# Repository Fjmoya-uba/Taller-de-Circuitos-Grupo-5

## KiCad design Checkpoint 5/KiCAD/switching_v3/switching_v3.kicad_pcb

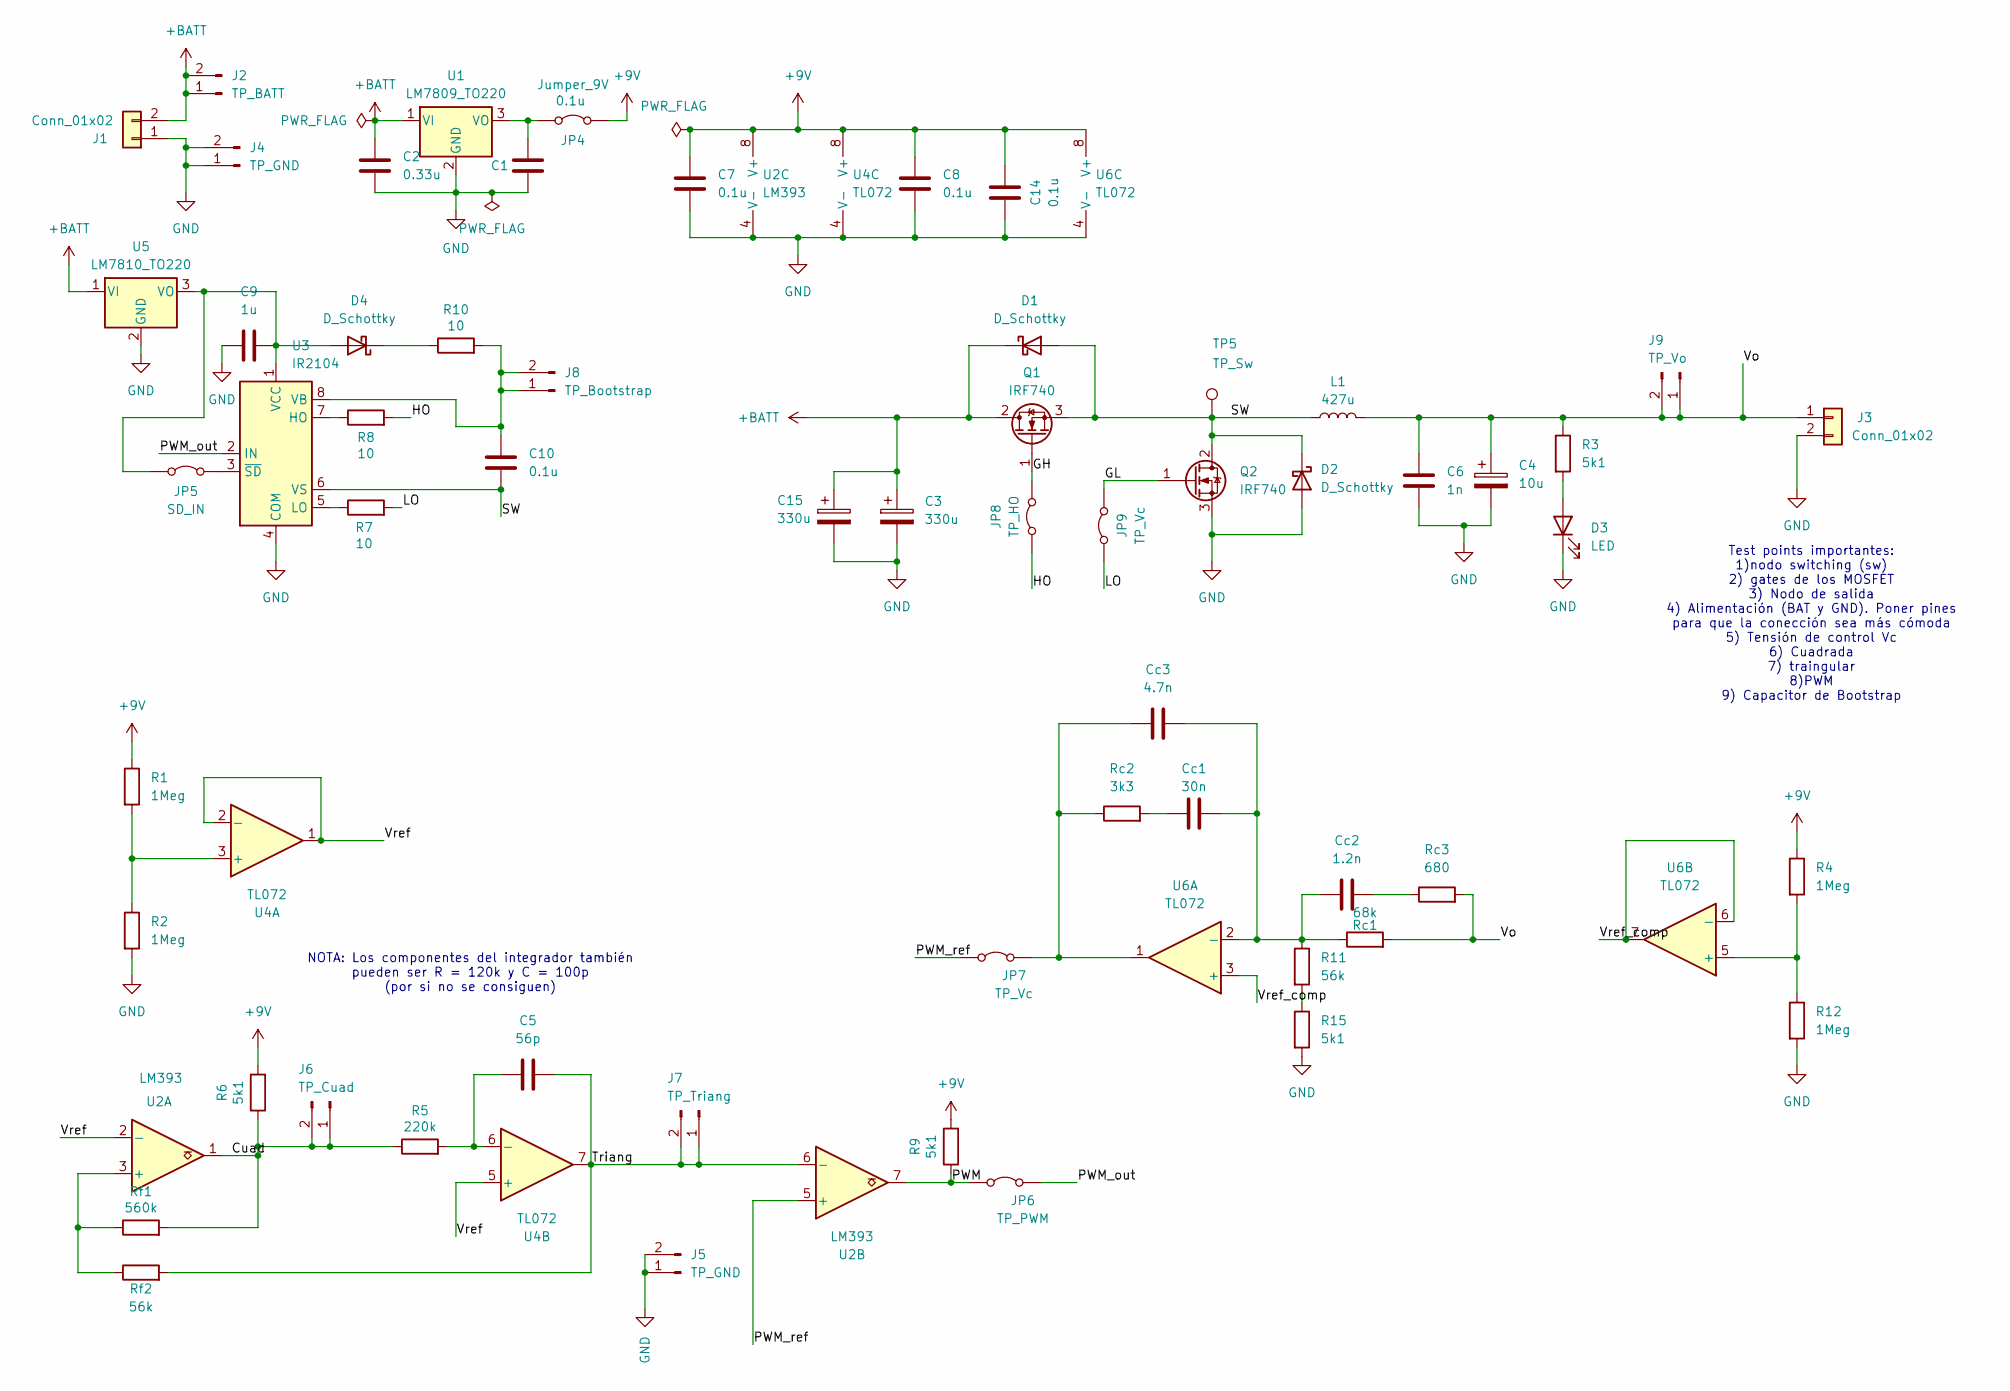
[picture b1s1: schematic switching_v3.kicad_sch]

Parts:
C1, C7, C8, C10, C14: 0.1u; C_Disc_D5.0mm_W2.5mm_P2.50mm
C2: 0.33u; C_Disc_D5.0mm_W2.5mm_P2.50mm
C3, C15: 330u; CP_Radial_D10.0mm_P5.00mm
C4: 10u; CP_Radial_D5.0mm_P2.50mm
C5: 56p; C_Disc_D5.0mm_W2.5mm_P2.50mm
C6: 1n; C_Disc_D14.5mm_W5.0mm_P10.00mm
C9: 1u; C_Disc_D8.0mm_W2.5mm_P5.00mm
Cc1: 30n; C_Disc_D5.0mm_W2.5mm_P2.50mm
Cc2: 1.2n; C_Disc_D5.0mm_W2.5mm_P2.50mm
Cc3: 4.7n; C_Disc_D5.0mm_W2.5mm_P2.50mm
D1, D2, D4: D_Schottky; D_DO-201AD_P12.70mm_Horizontal
D3: LED; LED_D5.0mm_IRGrey
J1, J3: Conn_01x02; TerminalBlock_MaiXu_MX126-5.0-02P_1x02_P5.00mm
J2: TP_BATT; PinHeader_1x02_P2.54mm_Vertical
J4, J5: TP_GND; PinHeader_1x02_P2.54mm_Vertical
J6: TP_Cuad; PinHeader_1x02_P2.54mm_Vertical
J7: TP_Triang; PinHeader_1x02_P2.54mm_Vertical
J8: TP_Bootstrap; PinHeader_1x02_P2.54mm_Vertical
J9: TP_Vo; PinHeader_1x02_P2.54mm_Vertical
JP4: Jumper_9V; PinHeader_1x02_P2.54mm_Vertical
JP5: SD_IN; PinHeader_1x02_P2.54mm_Vertical
JP6: TP_PWM; PinHeader_1x02_P2.54mm_Vertical
JP7, JP9: TP_Vc; PinHeader_1x02_P2.54mm_Vertical
JP8: TP_HO; PinHeader_1x02_P2.54mm_Vertical
L1: 427u; Transformer_37x44
Q1, Q2: IRF740; TO-220-3_Vertical
R1, R2, R4, R12: 1Meg; R_Axial_DIN0207_L6.3mm_D2.5mm_P7.62mm_Horizontal
R3, R6, R9, R15: 5k1; R_Axial_DIN0207_L6.3mm_D2.5mm_P7.62mm_Horizontal
R5: 220k; R_Axial_DIN0207_L6.3mm_D2.5mm_P7.62mm_Horizontal
R7, R8, R10: 10; R_Axial_DIN0207_L6.3mm_D2.5mm_P7.62mm_Horizontal
R11: 56k; R_Axial_DIN0207_L6.3mm_D2.5mm_P7.62mm_Horizontal
Rc1: 68k; R_Axial_DIN0207_L6.3mm_D2.5mm_P7.62mm_Horizontal
Rc2: 3k3; R_Axial_DIN0207_L6.3mm_D2.5mm_P7.62mm_Horizontal
Rc3: 680; R_Axial_DIN0207_L6.3mm_D2.5mm_P7.62mm_Horizontal
Rf1: 560k; R_Axial_DIN0207_L6.3mm_D2.5mm_P7.62mm_Horizontal
Rf2: 56k; R_Axial_DIN0207_L6.3mm_D2.5mm_P7.62mm_Horizontal
TP5: TP_Sw; PinHeader_1x01_P2.54mm_Vertical
U1: LM7809_TO220; TO-220-3_Vertical
U2: LM393; DIP-8_W7.62mm_Socket_LongPads
U3: IR2104; DIP-8_W7.62mm_Socket_LongPads
U4, U6: TL072; DIP-8_W7.62mm_Socket_LongPads
U5: LM7810_TO220; TO-220-3_Vertical

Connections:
+9V: C7.1, C8.1, C14.1, JP4.2 (B), R1.1, R4.1, R6.2, R9.2, U2.8 (V+), U4.8 (V+), U6.8 (V+)
+BATT: C2.1, C3.1, C15.1, D1.1 (K), J1.2, J2.1, J2.2, Q1.2 (D), U1.1 (VI), U5.1 (VI)
/Cuad: J6.1, J6.2, R5.1, R6.1, Rf1.2, U2.1
/GH: JP8.2 (B), Q1.1 (G)
/GL: JP9.2 (B), Q2.1 (G)
/HO: JP8.1 (A), R8.2
/LO: JP9.1 (A), R7.2
/PWM: JP6.1 (A), R9.1, U2.7
/PWM_out: JP6.2 (B), U3.2 (IN)
/PWM_ref: JP7.1 (A), U2.5 (+)
/SW: C10.2, D1.2 (A), D2.1 (K), L1.1, Q1.3 (S), Q2.2 (D), TP5.1 (1_1), U3.6 (VS)
/Triang: C5.1, J7.1, J7.2, Rf2.2, U2.6 (-), U4.7
/Vo: C4.1, C6.1, J3.1, J9.1, J9.2, L1.2, R3.1, Rc1.2, Rc3.2
/Vref: U2.2 (-), U4.1, U4.2 (-), U4.5 (+)
/Vref_comp: U6.3 (+), U6.6 (-), U6.7
GND: C1.2, C2.2, C3.2, C4.2, C6.2, C7.2, C8.2, C9.1, C14.2, C15.2, D2.2 (A), D3.1 (K), J1.1, J3.2, J4.1, J4.2, J5.1, J5.2, Q2.3 (S), R2.2, R12.2, R15.2, U1.2 (GND), U2.4 (V-), U3.4 (COM), U4.4 (V-), U5.2 (GND), U6.4 (V-)
unnamed: Cc1.1, Rc2.2
unnamed: Cc2.2, Rc3.1
unnamed: D3.2 (A), R3.2
unnamed: C9.2, D4.2 (A), JP5.1 (A), U3.1 (VCC), U5.3 (VO)
unnamed: D4.1 (K), R10.1
unnamed: C10.1, J8.1, J8.2, R10.2, U3.8 (VB)
unnamed: C1.1, JP4.1 (A), U1.3 (VO)
unnamed: JP5.2 (B), U3.3 (~SD)
unnamed: Cc3.1, JP7.2 (B), Rc2.1, U6.1
unnamed: R11.2, R15.1
unnamed: Rf1.1, Rf2.1, U2.3 (+)
unnamed: R8.1, U3.7 (HO)
unnamed: R7.1, U3.5 (LO)
unnamed: R1.2, R2.1, U4.3 (+)
unnamed: C5.2, R5.2, U4.6 (-)
unnamed: Cc1.2, Cc2.1, Cc3.2, R11.1, Rc1.1, U6.2 (-)
unnamed: R4.2, R12.1, U6.5 (+)

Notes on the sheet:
Test points importantes: 1)nodo switching (sw) 2) gates de los MOSFET 3) Nodo de salida 4) Alimentación (BAT y GND). Poner pines para que la conección sea más cómoda 5) Tensión de control Vc 6) Cuadrada 7) traingular 8)PWM 9) Capacitor de Bootstrap
NOTA: Los componentes del integrador también pueden ser R = 120k y C = 100p (por si no se consiguen)

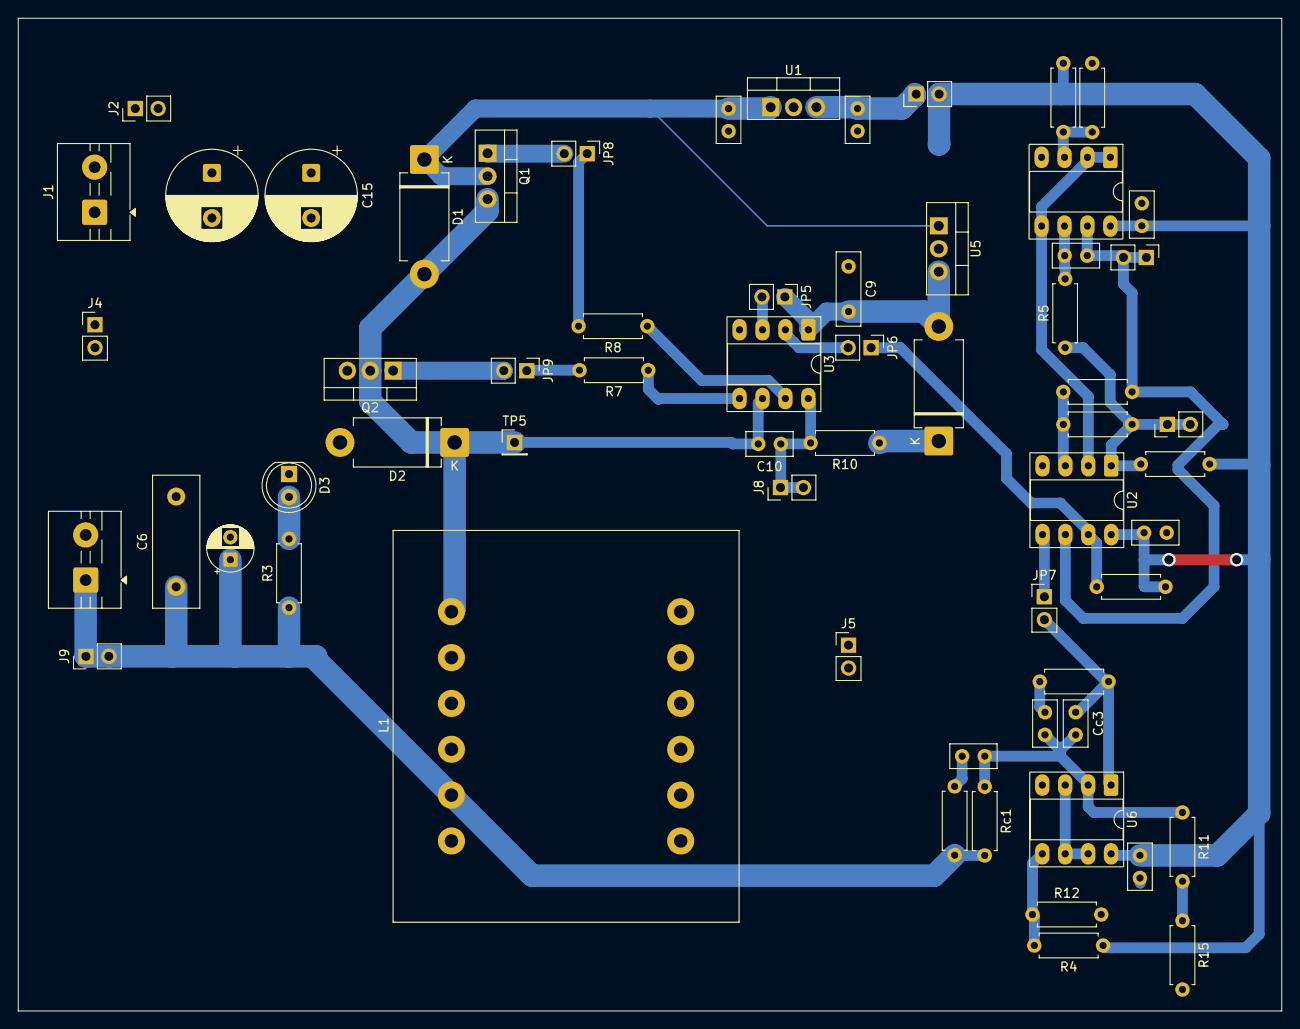
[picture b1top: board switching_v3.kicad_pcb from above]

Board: 2 copper layers, 140.0 x 110.0 mm, 62 parts (0 on the bottom side), 33 nets.

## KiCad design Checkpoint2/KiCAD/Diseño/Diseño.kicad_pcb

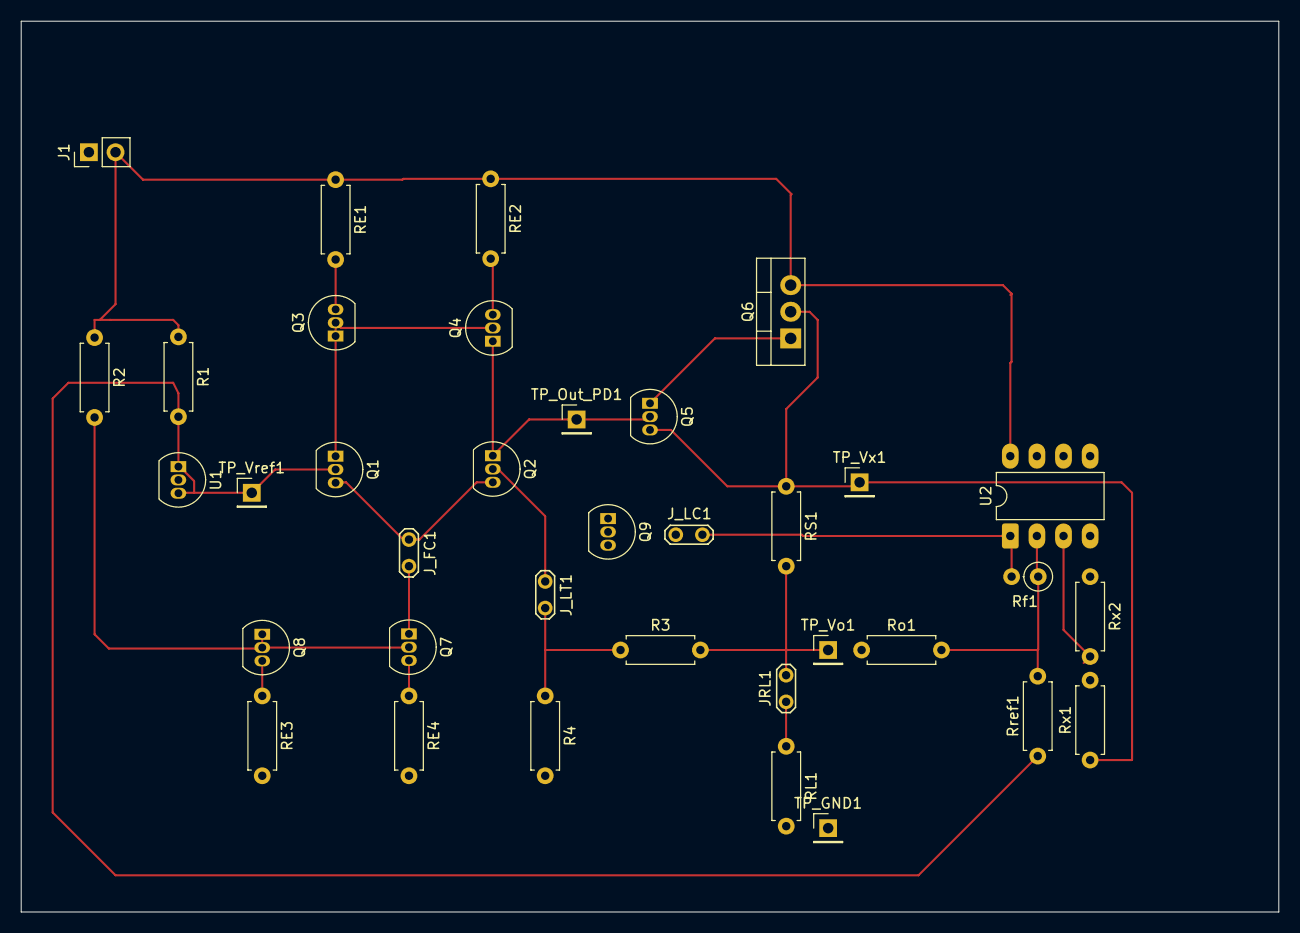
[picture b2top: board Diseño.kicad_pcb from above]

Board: 2 copper layers, 120.0 x 85.0 mm, 36 parts (0 on the bottom side), 22 nets.

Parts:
J1: Conn_01x02; PinHeader_1x02_P2.54mm_Vertical
JRL1: TestPoint_2Pads_Pitch2.54mm_Drill0.8mm
J_FC1: TestPoint_2Pads_Pitch2.54mm_Drill0.8mm
J_LC1: TestPoint_2Pads_Pitch2.54mm_Drill0.8mm
J_LT1: TestPoint_2Pads_Pitch2.54mm_Drill0.8mm
Q1, Q2, Q5, Q7, Q8, Q9: BC547; TO-92_Inline
Q3, Q4: BC557; TO-92_Inline
Q6: TIP32A; TO-220-3_Vertical
R1: 680; R_Axial_DIN0207_L6.3mm_D2.5mm_P7.62mm_Horizontal
R2: 4k7; R_Axial_DIN0207_L6.3mm_D2.5mm_P7.62mm_Horizontal
R3, R4: 10k; R_Axial_DIN0207_L6.3mm_D2.5mm_P7.62mm_Horizontal
RE1, RE2, RE3, RE4: 680; R_Axial_DIN0207_L6.3mm_D2.5mm_P7.62mm_Horizontal
RL1: R_Axial_DIN0207_L6.3mm_D2.5mm_P7.62mm_Horizontal
RS1: R_Axial_DIN0207_L6.3mm_D2.5mm_P7.62mm_Horizontal
Rf1: 10k; R_Axial_DIN0207_L6.3mm_D2.5mm_P2.54mm_Vertical
Ro1: 150; R_Axial_DIN0207_L6.3mm_D2.5mm_P7.62mm_Horizontal
Rref1: 1k2; R_Axial_DIN0207_L6.3mm_D2.5mm_P7.62mm_Horizontal
Rx1: 10k; R_Axial_DIN0207_L6.3mm_D2.5mm_P7.62mm_Horizontal
Rx2: 3k9; R_Axial_DIN0207_L6.3mm_D2.5mm_P7.62mm_Horizontal
TP_GND1: PinHeader_1x01_P2.54mm_Vertical
TP_Out_PD1: PinHeader_1x01_P2.54mm_Vertical
TP_Vo1: PinHeader_1x01_P2.54mm_Vertical
TP_Vref1: PinHeader_1x01_P2.54mm_Vertical
TP_Vx1: PinHeader_1x01_P2.54mm_Vertical
U1: TL431LP; TO-92_Inline
U2: LM358; DIP-8_W7.62mm_LongPads

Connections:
/Vf: J_LC1.2 (B), Rf1.2, U2.1
/Vo: JRL1.2 (B), R3.2, RS1.2, Ro1.1, TP_Vo1.1 (1_1)
/Vref: Q1.2 (B), R1.2, Rref1.1, TP_Vref1.1 (1_1), U1.1 (REF), U1.3 (K)
/Vx: Q5.3 (E), Q6.2 (C), RS1.1, Rx1.1, TP_Vx1.1 (1_1)
GND: J1.1, Q9.3 (E), R4.2, RE3.2, RE4.2, RL1.2, Rx2.1, TP_GND1.1 (1_1), U1.2 (A), U2.4 (V-)
unnamed: J1.2, Q6.3 (E), R1.1, R2.1, RE1.1, RE2.1, U2.8 (V+)
unnamed: JRL1.1 (A), RL1.1
unnamed: J_FC1.1 (A), Q1.3 (E), Q2.3 (E)
unnamed: J_FC1.2 (B), Q7.1 (C)
unnamed: J_LC1.1 (A), Q9.2 (B)
unnamed: J_LT1.1 (A), Q2.2 (B)
unnamed: J_LT1.2 (B), R3.1, R4.1
unnamed: Q1.1 (C), Q3.1 (C), Q3.2 (B), Q4.2 (B)
unnamed: Q2.1 (C), Q4.1 (C), Q5.2 (B), Q9.1 (C), TP_Out_PD1.1 (1_1)
unnamed: Q3.3 (E), RE1.2
unnamed: Q4.3 (E), RE2.2
unnamed: Q5.1 (C), Q6.1 (B)
unnamed: Q7.2 (B), Q8.1 (C), Q8.2 (B), R2.2
unnamed: Q7.3 (E), RE4.1
unnamed: Q8.3 (E), RE3.1
unnamed: Rx1.2, Rx2.2, U2.3 (+)
unnamed: Rf1.1, Ro1.2, Rref1.2, U2.2 (-)

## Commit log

2026-03-28 final for today
2026-04-08 Archivos de KiCAD
2026-04-09 hice cositas
2026-04-09 Funciona
2026-04-09 19.54
2026-04-09 Arreglando cosas
2026-04-10 seguimos
2026-04-10 Agrego las simulaciones con sus gráficos
2026-04-10 Correcciones de las simulaciones
2026-04-10 Cosas
2026-04-11 ganancia de lazo para varias cargas
2026-04-11 informe final
2026-04-12 Reorganización
2026-04-16 Agrego el .gitignore para filtrar archivos de KiCAD
2026-04-16 Primer diseño. Muchas dudas
2026-04-16 eliminé prueba.txt
2026-04-17 vamos a ver dijo el ciego
2026-04-17 actualizacion
2026-06-02 simulación diodo rueda libre
2026-06-03 Papers sobre la buck
2026-06-04 simulaciones CP5
2026-06-04 medicion del tp
2026-06-08 avances cp5
2026-06-08 le cambié el nombre a una simulación
2026-06-09 Anotaciones sobre la hoja de datos de TI
2026-06-13 caracterización inductor
2026-06-14 Cuentas sobre la compensación
2026-06-17 Cuentas compensación
2026-06-18 simulaciones
2026-06-18 Elimino archivos innecesarios.
2026-06-18 datasheet diodo schottky
2026-06-18 circuito bootstrap + nota de aplicación
2026-06-19 intentando hacer el pcb
2026-06-19 agregué PWM a cp5
2026-06-20 Agrego datasheets
2026-06-20 PWM arreglado
2026-06-21 corregí el cálculo del inductor
2026-06-21 Corregí el valor del inductor
2026-06-21 avances PCB
2026-06-22 correción PCB
2026-06-23 lista de materiales
2026-06-24 nueva salida de frabricacion
2026-06-25 agregué el LM7810
2026-06-25 PWM change
2026-06-26 fotos simulaciones
2026-06-27 Datasheets
2026-06-27 Agrego informe
2026-06-30 commit final
